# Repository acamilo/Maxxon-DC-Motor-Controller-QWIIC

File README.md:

# OSH Park-compatible 2 Layer KiCad Template

This is a KiCad template to simplify making printed circuit boards.  

It comes with all the design rules to meet the 2-layer OSH Park specs and stackup. 

- <a href="http://docs.oshpark.com/services/two-layer/">OSH Park Two Layer Specs</a>
- <a href="http://docs.oshpark.com/design-tools/kicad">OSH Park KiCad help</a>

### Instructions

1. Open KiCad.
1. Open Preferences > Configure Paths and note the value of 'KICAD_PTEMPLATES'.
1. <a href="https://github.com/wickerbox/wickerlib/blob/master/templates/oshpark-2layer-template.zip?raw=true">Download the template zip</a> and extract into the location of 'KICAD_PTEMPLATES'.
1. In KiCad, open File > New Project > New Project from Template.
1. Select the location of your new project. The name of the folder will be the name of your project.
1. The templates with folders in the 'KICAD_PTEMPLATES' are listed under 'Portable Templates" tab.
1. Select the template and click 'OK'.
1. Your project now exists, so you can open EESchema and PCBNew and design as usual.

# Maxxon-DC-Motor-Controller-QWIIC

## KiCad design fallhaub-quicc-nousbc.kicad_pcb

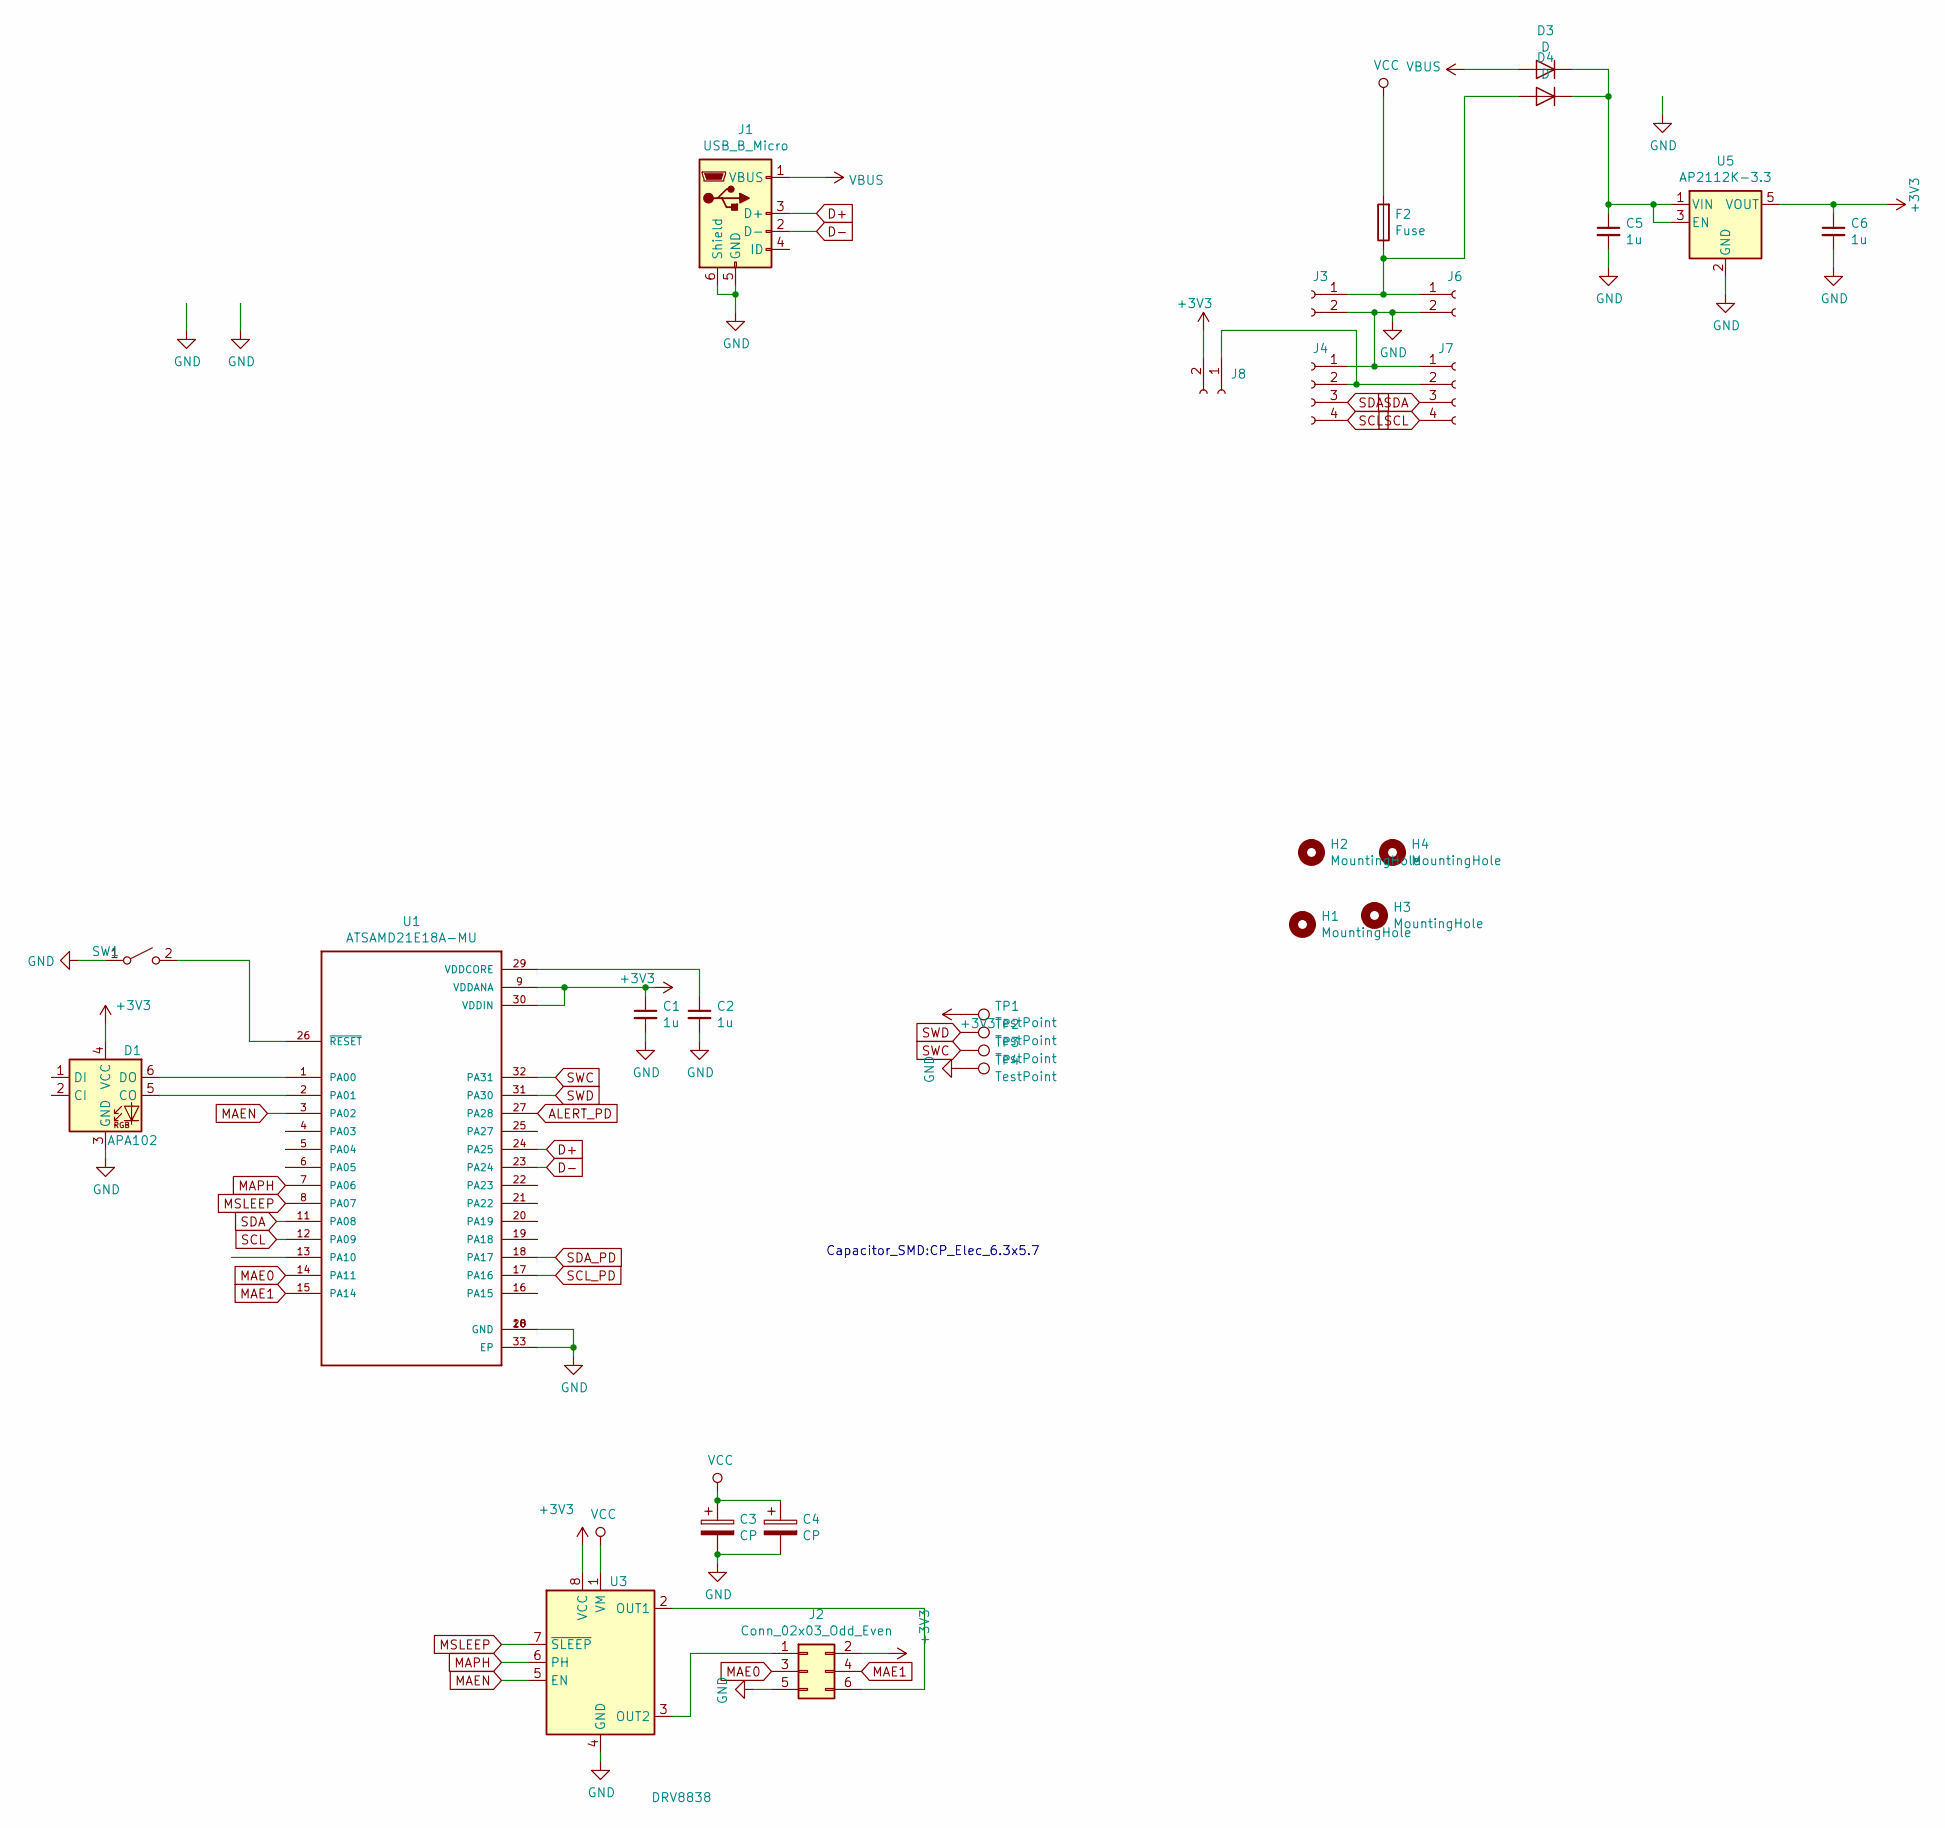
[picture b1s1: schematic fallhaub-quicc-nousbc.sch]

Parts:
C1, C2, C5, C6: 1u; C_0603_1608Metric
C3, C4: CP; CP_Elec_6.3x5.7
D1: APA102; LED_RGB_PLCC-6
D3, D4: D; D_0603_1608Metric
F2: Fuse; NANO-0154-OMNI-BLOK-Fuse-Holder
H1, H2, H3, H4: MountingHole; MountingHole_2.2mm_M2
J1: USB_B_Micro; USB_Micro-B_Molex_47346-0001
J2: Conn_02x03_Odd_Even; PinSocket_2x03_P2.54mm_Vertical
J3, J6: Conn_01x02_Female; JST_PH_B2B-PH-SM4-TB_1x02-1MP_P2.00mm_Vertical
J4, J7: Conn_01x04_Female; JST_SH_BM04B-SRSS-TB_1x04-1MP_P1.00mm_Vertical
J8: Conn_01x02_Female; SolderJumper-2_P1.3mm_Open_RoundedPad1.0x1.5mm
SW1: SW_SPST; SW_SPST_CK_KXT3
TP1, TP2, TP3, TP4: TestPoint; TestPoint_Pad_D2.0mm
U1: ATSAMD21E18A-MU; QFN50P500X500X100-33N
U3: DRV8838; WSON-8-1EP_2x2mm_P0.5mm_EP0.9x1.6mm
U5: AP2112K-3.3; SOT-23-5

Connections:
+3V3: C1.1, C6.1, D1.4 (VCC), J2.2, J8.2, TP1.1, U1.9 (VDDANA), U1.30 (VDDIN), U3.8 (VCC), U5.5 (VOUT)
ALERT_PD: U1.27 (PA28)
D+: J1.3 (D+), U1.24 (PA25)
D-: J1.2 (D-), U1.23 (PA24)
GND: C1.2, C2.2, C3.2, C4.2, C5.2, C6.2, D1.3 (GND), J1.5 (GND), J1.6 (Shield), J2.5, J3.2, J4.1, J6.2, J7.1, SW1.1 (A), TP4.1, U1.10 (GND), U1.28 (GND), U1.33 (EP), U3.4 (GND), U3.9 (GND), U5.2 (GND)
MAE0: J2.3, U1.14 (PA11)
MAE1: J2.4, U1.15 (PA14)
MAEN: U1.3 (PA02), U3.5 (EN)
MAPH: U1.7 (PA06), U3.6 (PH)
MSLEEP: U1.8 (PA07), U3.7 (~SLEEP)
unnamed: C2.1, U1.29 (VDDCORE)
unnamed: C5.1, D3.1 (K), D4.1 (K), U5.1 (VIN), U5.3 (EN)
unnamed: D1.5 (CO), U1.2 (PA01)
unnamed: D1.6 (DO), U1.1 (PA00)
unnamed: D4.2 (A), F2.1, J3.1, J6.1
unnamed: J2.1, U3.3 (OUT2)
unnamed: J2.6, U3.2 (OUT1)
unnamed: J4.2, J7.2, J8.1
unnamed: SW1.2 (B), U1.26 (~RESET~)
SCL: J4.4, J7.4, U1.12 (PA09)
SCL_PD: U1.17 (PA16)
SDA: J4.3, J7.3, U1.11 (PA08)
SDA_PD: U1.18 (PA17)
SWC: TP3.1, U1.32 (PA31)
SWD: TP2.1, U1.31 (PA30)
VBUS: D3.2 (A), J1.1 (VBUS)
VCC: C3.1, C4.1, F2.2, U3.1 (VM)

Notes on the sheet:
Capacitor_SMD:CP_Elec_6.3x5.7

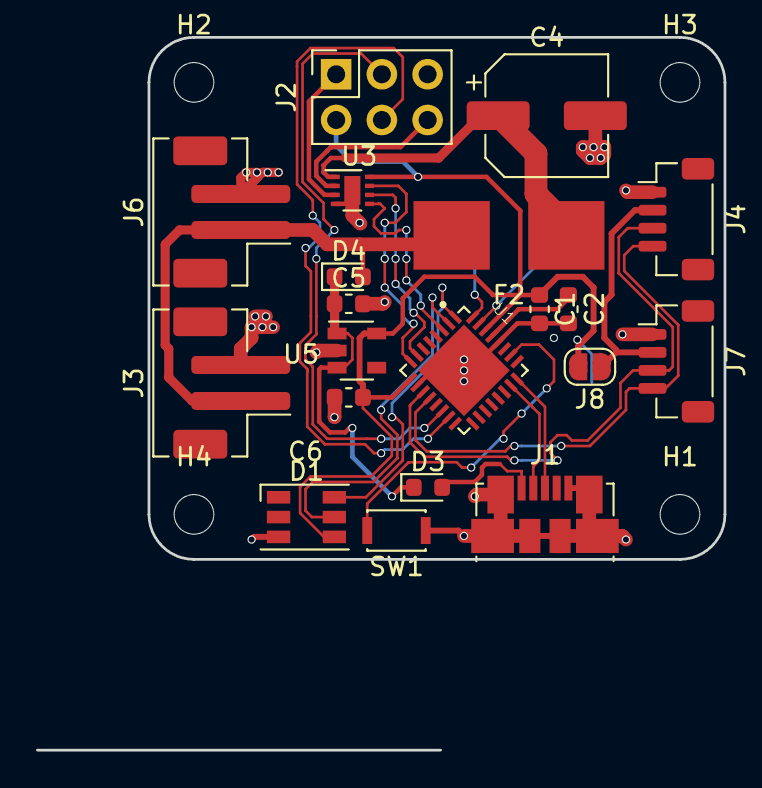
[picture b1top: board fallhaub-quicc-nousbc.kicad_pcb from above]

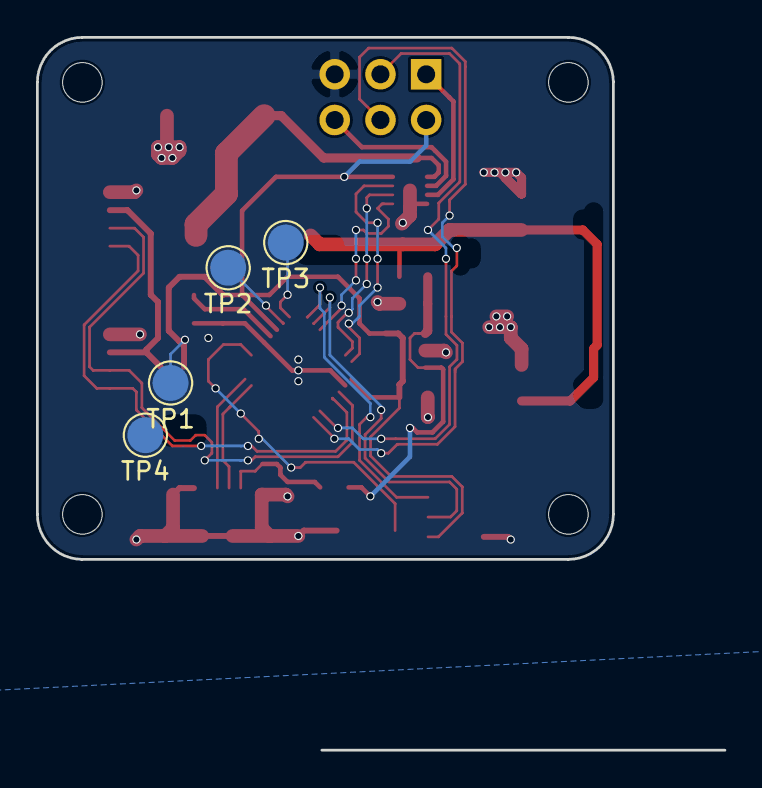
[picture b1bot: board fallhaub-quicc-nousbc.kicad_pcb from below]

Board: 2 copper layers, 38.2 x 39.6 mm, 28 parts (4 on the bottom side), 24 nets.

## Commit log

2020-04-30 gitignore for kicad
2020-04-30 Layout done, ready for review
2020-05-07 No PD version.
